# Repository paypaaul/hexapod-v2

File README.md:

# Hexapod v2

Robot esapode a 18 gradi di libertà (6 zampe × 3 servo MG996R), stampato in 3D e comandato da un ESP32-S3 con camera e una SSC-32. Progetto personale, in fase di progettazione CAD.

Altri render: [da dietro](docs/immagini/render-montato-post.png), [di fianco](docs/immagini/render-montato-fianco.png), [esploso della zampa](docs/immagini/render-esploso-zampa.png), [esploso del corpo](docs/immagini/render-esploso-corpo.png).

## Dove guardare

| Documento | Contenuto |
|---|---|
| [Progetto meccanico](docs/progetto-meccanico.md) | zampa, corpo, assieme, verifiche di movimento, cavi, massa |
| [Decisioni](docs/decisioni.md) | registro delle scelte con il perché |
| [BOM](docs/BOM.md) | distinta base, schema di alimentazione, viteria, domande aperte |
| [Studio dei componenti](docs/studio-componenti.md) | servo, alimentazione, batteria, giunti, stampa |
| [Dimensionamento](docs/dimensionamento.md) | massa, geometria, coppie e assetti |
| [Dimensioni dei componenti](docs/dimensioni-componenti.md) | quote dei componenti con la fonte |
| [Ricerca](docs/ricerca/) | proposte e revisioni indipendenti di zampa e corpo |

## Cartelle

- `cad/script/`: script Python che costruiscono il modello in Fusion (`corpo.py`, `zampa.py`, `assieme.py`).
- `cad/stl/`: STL delle parti già pronte per i provini.
- `cad/modelli/`: fonti dei modelli STEP di terzi.
- `cad/render/`: render schematici del modello.
- `calc/`: calcoli di statica, andature, escursioni e cavi.

Lo stato del lavoro e i prossimi passi sono in [CLAUDE.md](CLAUDE.md).

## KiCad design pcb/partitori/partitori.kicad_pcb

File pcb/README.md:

# Circuiti stampati (PCB)

Progetti KiCad delle schede del robot. Piano, scelte e fasi: `docs/piano-pcb.md` (D-078).

## Versione di KiCad

**KiCad 10.0.7**. Gli script e la CI usano questa; un'altra 10.0.x va provata prima (formato dei file, DRC).
Sul Mac: `/Applications/KiCad/KiCad.app`, con `kicad-cli` in `Contents/MacOS/` e il Python di KiCad (3.9, con `pcbnew`) in `Contents/Frameworks/Python.framework/Versions/Current/bin/python3`. I percorsi si cambiano con le variabili `KICAD_CLI`, `KICAD10_SYMBOL_DIR` e `KICAD10_FOOTPRINT_DIR`.

## Come sono fatti i progetti

Schema e PCB **si generano da script**, e i file di KiCad sono il risultato. Una modifica si fa nello script e si rigenera: una modifica fatta solo nell'editor si perde alla rigenerazione. L'editor serve per guardare (schema, PCB, 3D) e per provare; quello che si vuole tenere torna nello script.

| Passo | Script | Python |
|---|---|---|
| copie dei simboli e delle impronte standard in `librerie/` | `script/librerie.py` (`--controlla`; vuole le librerie di KiCad installate) | qualunque |
| simboli e impronte disegnati per il robot (ESP32 RE1.3, D24V22F5, PTC e 470 µF sdraiati) in `librerie/hex2.*` | `script/propri.py` (`--controlla`) | qualunque |
| schema: simboli, fili, etichette, segni di non collegato | `<scheda>/genera_schema.py`, con `script/schema_kicad.py` | qualunque, con `kicad-cli` |
| PCB: impronte con le reti della netlist, contorno, piste, vie, riempimenti | `<scheda>/genera_pcb.py`, con `script/scheda_kicad.py` | di KiCad (`pcbnew`) |
| ERC, DRC con la parità dello schema (se c'è già il PCB) e reti contro la guida | `script/controlla.py <cartella>` | qualunque, con `kicad-cli` |
| regole del DRC: fonte unica `regole/hex2.kicad_dru`, copiata in ogni progetto come `<nome>.kicad_dru` | `script/regole.py` (`--controlla`) | qualunque |
| contorno, fori Ø2,4 e zone senza rame dalle quote del CAD | `script/genera_contorni.py` (`--controlla <file>.kicad_pcb`); nel PCB `Scheda.contorni_dal_cad` | qualunque |
| reti di KiCad contro `guida/schemi/sorgenti/*_def.py`, con le differenze volute in `aggiunte.yaml` | `script/verifica_reti.py <scheda> <file>.net` | qualunque, con PyYAML |

Piazzamento sul lato B: KiCad ribalta l'impronta specchiando la Y; con 180 gradi in più la scheda si guarda dall'alto del robot (X specchiata). `pcb/stato.yaml` dice in che fase è ogni scheda: in "piazzamento" `controlla.py` conta a parte le connessioni da sbrogliare e gli avvisi di serigrafia.

Regole degli script:
- lo schema ha un tratto di filo e un'etichetta su ogni pin collegato, e il segno di non collegato sui pin liberi. Un pin senza né l'uno né l'altro, o una rete su un pin che non esiste, fermano il generatore prima di KiCad;
- gli identificativi sono ripetibili (uuid derivati dai nomi nello schema, generatore con il seme nel PCB): rigenerare senza modifiche dà gli stessi file;
- lo schema passa da `kicad-cli sch upgrade --force`, così è nel formato in cui lo salverebbe KiCad;
- il PCB copia nelle impronte quello che copierebbe "Aggiorna PCB dallo schema": percorso del simbolo, foglio, campi, esclusione dalla distinta, non montare;
- `controlla.py` fallisce su qualunque rilievo, anche sugli avvisi.

Terna: x = X del robot + 100, y = 100 − Y del robot (KiCad ha la Y verso il basso). Le schede si guardano dall'alto del robot; i componenti della scheda del carapace stanno sul retro (B.Cu). Lo STEP con `--user-origin 100x100mm` torna nella terna del robot (`cad/CLAUDE.md`, STEP delle PCB).

Numeri dei pin per `verifica_reti.py`: ESP32 (U1) da 1 a 20 la fila `ESP_L` dalla coda alla testa, da 21 a 40 la fila `ESP_R` nello stesso verso; D24V22F5 (U2) PG 1, EN 2, VIN 3, GND 4, VOUT 5; condensatori con il + sul pin 1; resistenze e diodi a due fori con il primo foro dei `*_def.py` sul pin 1 (per i diodi il catodo). Le impronte di U1 e U2 si fanno con questa numerazione.

Testata J2 del carapace: pad n = polo n del cavo piatto; poli dispari sulla fila lato chiave, a 4,38 dalla scatola (S-26). Da provare sulla dima con la spina (F5).

**Regole del DRC**: se una sola regola di `regole/hex2.kicad_dru` è scritta male, KiCad ignora tutto il file senza avvisi e il DRC esce a zero. Ogni modifica alle regole passa da `tests/test_pcb.py` (il caso della pista stretta usa la copia vera delle regole) e una regola nuova ha il suo caso di controllo.

Librerie: `librerie/hex2_kicad.kicad_sym` (simboli copiati da KiCad 10, appiattiti) e `librerie/hex2.pretty` (impronte copiate e, più avanti, quelle disegnate per il robot). Le tabelle `sym-lib-table` e `fp-lib-table` di ogni progetto puntano solo lì.

## Schede

| Cartella | Scheda | Stato |
|---|---|---|
| `prova/` | scheda di prova del metodo, caso di riferimento della CI | schema e PCB |
| `basetta/` | PCB-B, basetta dell'ESP32 (piano 4.1), **quattro strati** | schema (R1, D-079, ritocchi di F4 in D-083); piazzamento e sbroglio da script con DRC a zero (D-083); dima e stampe per R2; serigrafia da fare |
| `carapace/` | PCB-C, scheda del carapace (piano 4.2) | schema (R1, D-079), piazzamento e sbroglio da script con DRC a zero (D-082); dima, render e stampa 1:1 per R2 (F5) |
| `partitori/` | PCB-P, scheda dei partitori, **quattro strati** (sullo stesso pannello della basetta) | schema, piazzamento e sbroglio da script con DRC a zero (D-084), sagoma di prova fino alla 2.1.9 del CAD; dima e stampe |

## Prova del metodo (F1, 18 ottobre 2026)

Scheda di prova in `prova/`: buffer SN74AHCT125N a cinque unità (quattro porte e l'alimentazione) in DIP-14, ponticello a tre piazzole, resistenza a reoforo, condensatore 0805, strip 1 × 4, punto di prova, due PWR_FLAG.

| Passo del piano (5.2) | Esito |
|---|---|
| 1. schema da script, con simboli, etichette e fili, che passa l'ERC | **riuscito**: ERC a zero rilievi. La netlist di KiCad è uguale alle reti dello script. Caso di controllo: un pin scollegato e un'alimentazione senza PWR_FLAG danno 3 errori (`pin_not_connected`, `pin_not_driven`, `power_pin_not_driven`) |
| 2. PCB con le impronte e le reti assegnate alle piazzole da `pcbnew` | **riuscito**: impronte dalla libreria del progetto, percorso del simbolo, reti della netlist |
| 3. piste e riempimento di massa da script | **riuscito**: piste su F.Cu, due vie, riempimento su B.Cu riempito da `ZONE_FILLER` |
| 4. DRC con `--schematic-parity` a zero, e un caso di controllo che fallisce | **riuscito**: zero violazioni, zero connessioni mancanti, zero rilievi di parità. Controlli: una pista tolta dà 2 `unconnected_items`; una piazzola con la rete sbagliata dà corto, ponte di maschera, connessione mancante e `net_conflict` di parità |

**Esito: schema, piazzamento e sbroglio li fa l'agente da script**, e l'utente rivede nell'editor e nei render. La colonna "Chi" del piano resta com'è.

Cose imparate nella prova, che il codice già tiene in conto:
- `board.GetLayerID('F.SilkS')` dà UNDEFINED (vuole i nomi utente): si usano le costanti `pcbnew.F_SilkS`;
- `pcbnew.NewBoard(percorso)` apre il `.kicad_pro` accanto e lo completa con i valori predefiniti, senza togliere quelli scritti prima;
- le istanze dei simboli non devono portare `ki_keywords` e `ki_fp_filters`: KiCad le tiene solo nella libreria, e copiate nelle impronte danno avvisi di parità e scritte sulla serigrafia;
- ogni unità di un simbolo a più unità elenca tutti i pin del simbolo, altrimenti KiCad dà ai mancanti un uuid a caso;
- con `--exit-code-violations` il DRC esce con 5 solo per gli errori: i rilievi di parità sono avvisi. Per questo `controlla.py` legge il JSON.

## Sbroglio

Lo sbroglio della basetta si rifà con `$KP pcb/basetta/sbroglia.py` (circa 3 minuti) e scrive `basetta/piste.json`, che `genera_pcb.py` rimette nel PCB: la CI non ha bisogno di strumenti esterni. Passi:
1. `script/sbroglio.py`, instradatore a griglia del progetto (Python puro, A*, 0,1 mm, tratti a 45°), per le reti con le regole a coppie del `.kicad_dru`: potenza, VBAT a 1 mm, segnali a 5 V a 1 mm dai pin dell'ESP32;
2. `script/freerouting.py` con **Freerouting 2.5.0** (`~/tools/freerouting/freerouting-2.5.0.jar`, da github.com/freerouting/freerouting) e **OpenJDK di Homebrew** (`brew install openjdk`, Java 25 o successivo) per le altre reti. Telemetria spenta da riga di comando e in `~/Library/Application Support/freerouting/freerouting.json`; niente piste ristrette ai pin. La versione nativa `freerouting-cli` si blocca allo sbroglio (errore di serializzazione di GraalVM): non si usa;
3. di nuovo `sbroglio.py`, sui quattro strati, per le reti che Freerouting lascia aperte o con un errore.

Dopo `ImportSpecctraSES` gli oggetti di `pcbnew` di quel processo non si leggono più dal Python: la lettura e la rifinitura girano in un processo nuovo. Le classi di rete (larghezze, VBAT a 1 mm) stanno nel `.kicad_pro`, scritte da `genera_pcb.py`, perché Freerouting non legge il `.kicad_dru`.

## Dime (F5)

Prima di ordinare, ogni scheda si prova con una **dima stampata 1:1**: la sola scheda, senza rame, con la sagoma e i fori del PCB, nella terna del robot (`cad/stl/attrezzi/Dima_PCB_<Scheda>.stl`, da `script/dima.py`, Python di KiCad). I fori dei pin sono allargati di 0,4 mm (`gio_stampa` per lato), quelli Ø2,4 delle viti no: se la M2 passa e centra l'inserto nella dima, passa anche nella scheda. La dima è spessa 1,5 (la scheda 1,6). Con la dima ci sono i render e la stampa 1:1 (`script/stampe.py`, in `docs/immagini/pcb/`): la stampa va fatta al 100 % e controllata col righello sulla sagoma (PCB-C: 21,5 mm da coda a testa, 48 fra le punte delle ali).

**PCB-C** (`Dima_PCB_Carapace.stl`), cosa provare e cosa riportare:
1. **J2 Würth** infilata dal lato dei componenti (sotto, come nel robot): i 16 pin entrano senza forzare e la scatola arriva a filo del bordo di coda.
2. **Polo 1 di J2 (S-26)**: si innesta la spina IDC del cavo piatto (la chiave la fa entrare in un verso solo). Il polo 1 dell'impronta è il foro quadrato, sulla fila lontana dalla scatola, verso +Y. Col multimetro in continuità fra il filo rosso del cavo (polo 1) e i pin che escono dalla dima: il filo rosso deve dare continuità con il pin del foro quadrato. Se la dà con il pin accanto, sulla fila vicina alla scatola, l'impronta va rovesciata prima dell'ordine.
3. **CE1** (470 µF) in piedi sotto l'ala +Y, con il + sulla piazzola quadrata, e i due fili del pulsante nelle piazzole dell'ala −Y.
4. **Nel carapace** (quando è stampato, con gli inserti M2): quattro M2 × 4 sugli inserti; le viti centrano gli inserti, le ali non toccano, J2 sta nella sua sede, CE1 non tocca il dorso.

**PCB-B** (`Dima_PCB_Basetta.stl`):
1. **strip femmina** dell'ESP32 a 25,4 (P-005), con i contatti dei pin 27, 28, 30 e 40 sfilati (varchi, D-083); l'ESP32 RE1.3 innestato: si misurano i 8,5 mm e si guarda che U2, U3, il fusibile, D1 e le sei resistenze in piedi passino sotto il suo retro;
2. **D24V22F5** appoggiato sulla dima con i pin senza il distanziale: i componenti di sotto entrano nell'apertura e il modulo sta piano;
3. **U3** (DIP-14), PTC1 sdraiato, D1, le resistenze in piedi (alte non più di 7,5 dalla scheda) e R11, R12;
4. sul vassoio: quattro M2 × 5 nelle colonne, la dima appoggia piana e le code dei reofori non toccano.

Esito: una riga per prova (va / non va, con la misura se non va) in fondo a `docs/piano-pcb.md`.

## Comandi

```
KP=/Applications/KiCad/KiCad.app/Contents/Frameworks/Python.framework/Versions/Current/bin/python3
python3 pcb/script/librerie.py
python3 pcb/prova/genera_schema.py
$KP pcb/prova/genera_pcb.py
python3 pcb/script/controlla.py pcb/prova
$KP pcb/basetta/sbroglia.py
$KP pcb/partitori/sbroglia.py
python3 pcb/script/gerber.py basetta partitori carapace   # zip in build/gerber/ per jlcpcb.com
$KP pcb/script/dima.py carapace
python3 pcb/script/stampe.py carapace
python3 pcb/script/regole.py --controlla
.venv/bin/python -m pytest tests/test_pcb.py -q
```

Nella CI il job `pcb` installa KiCad dal PPA (`ppa:kicad/kicad-10.0-releases`, senza le librerie), controlla che la versione sia quella scritta qui sopra e fa regole, ERC e DRC di ogni progetto, contorni e `tests/test_pcb.py`. I rapporti JSON restano fra gli artefatti (`pcb-rapporti`).

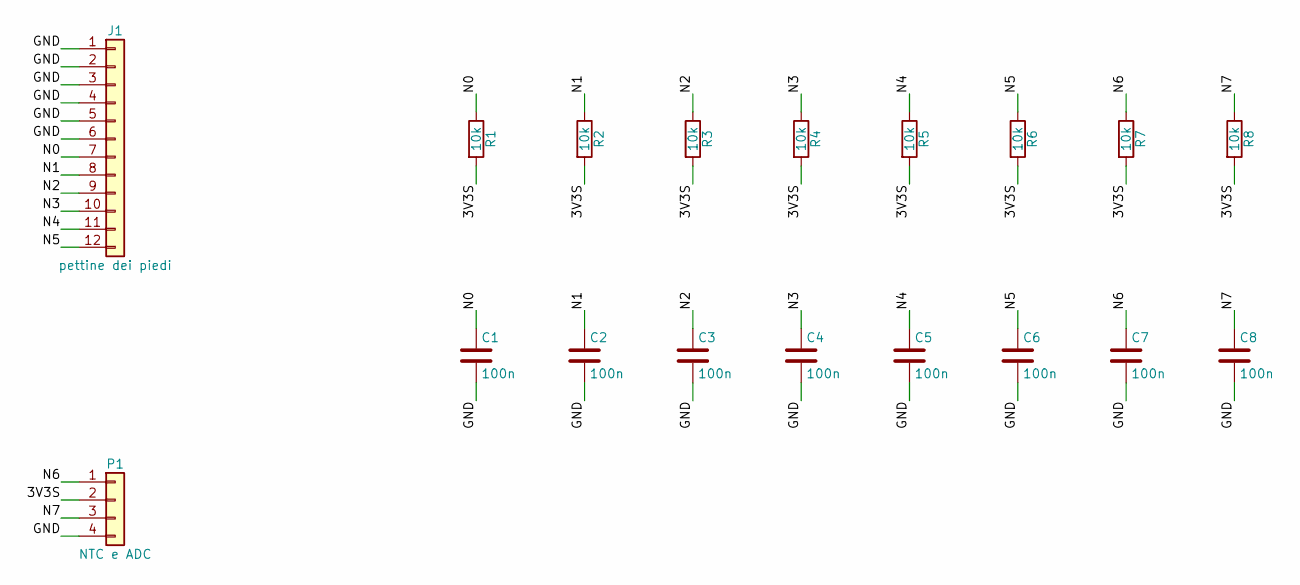
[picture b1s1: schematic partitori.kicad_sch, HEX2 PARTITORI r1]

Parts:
C1, C2, C3, C4, C5, C6, C7, C8: 100n; C_0805_2012Metric
J1: pettine dei piedi; Pettine_JR_2x06_P2.54_File5.08
P1: NTC e ADC; Fili_2x02_P2.54mm_D1.7
R1, R2, R3, R4, R5, R6, R7, R8: 10k; R_0805_2012Metric

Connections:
/3V3S: P1.2, R1.2, R2.2, R3.2, R4.2, R5.2, R6.2, R7.2, R8.2
/GND: C1.2, C2.2, C3.2, C4.2, C5.2, C6.2, C7.2, C8.2, J1.1, J1.2, J1.3, J1.4, J1.5, J1.6, P1.4
/N0: C1.1, J1.7, R1.1
/N1: C2.1, J1.8, R2.1
/N2: C3.1, J1.9, R3.1
/N3: C4.1, J1.10, R4.1
/N4: C5.1, J1.11, R5.1
/N5: C6.1, J1.12, R6.1
/N6: C7.1, P1.1, R7.1
/N7: C8.1, P1.3, R8.1

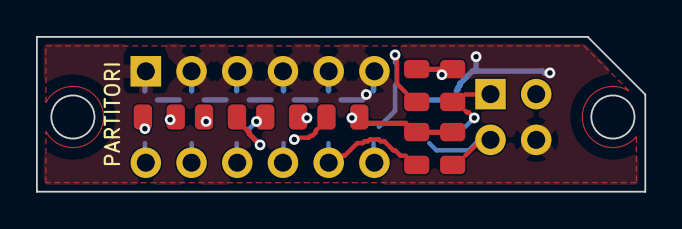
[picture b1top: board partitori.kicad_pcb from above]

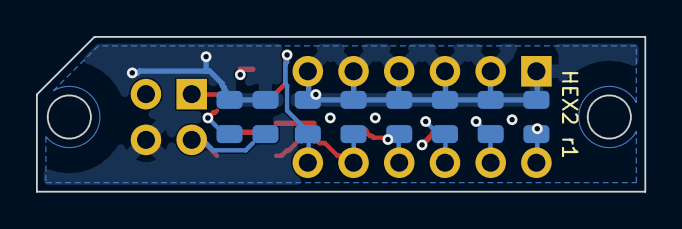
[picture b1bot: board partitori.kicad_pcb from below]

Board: 4 copper layers, 33.8 x 8.6 mm, 18 parts (8 on the bottom side), 10 nets.

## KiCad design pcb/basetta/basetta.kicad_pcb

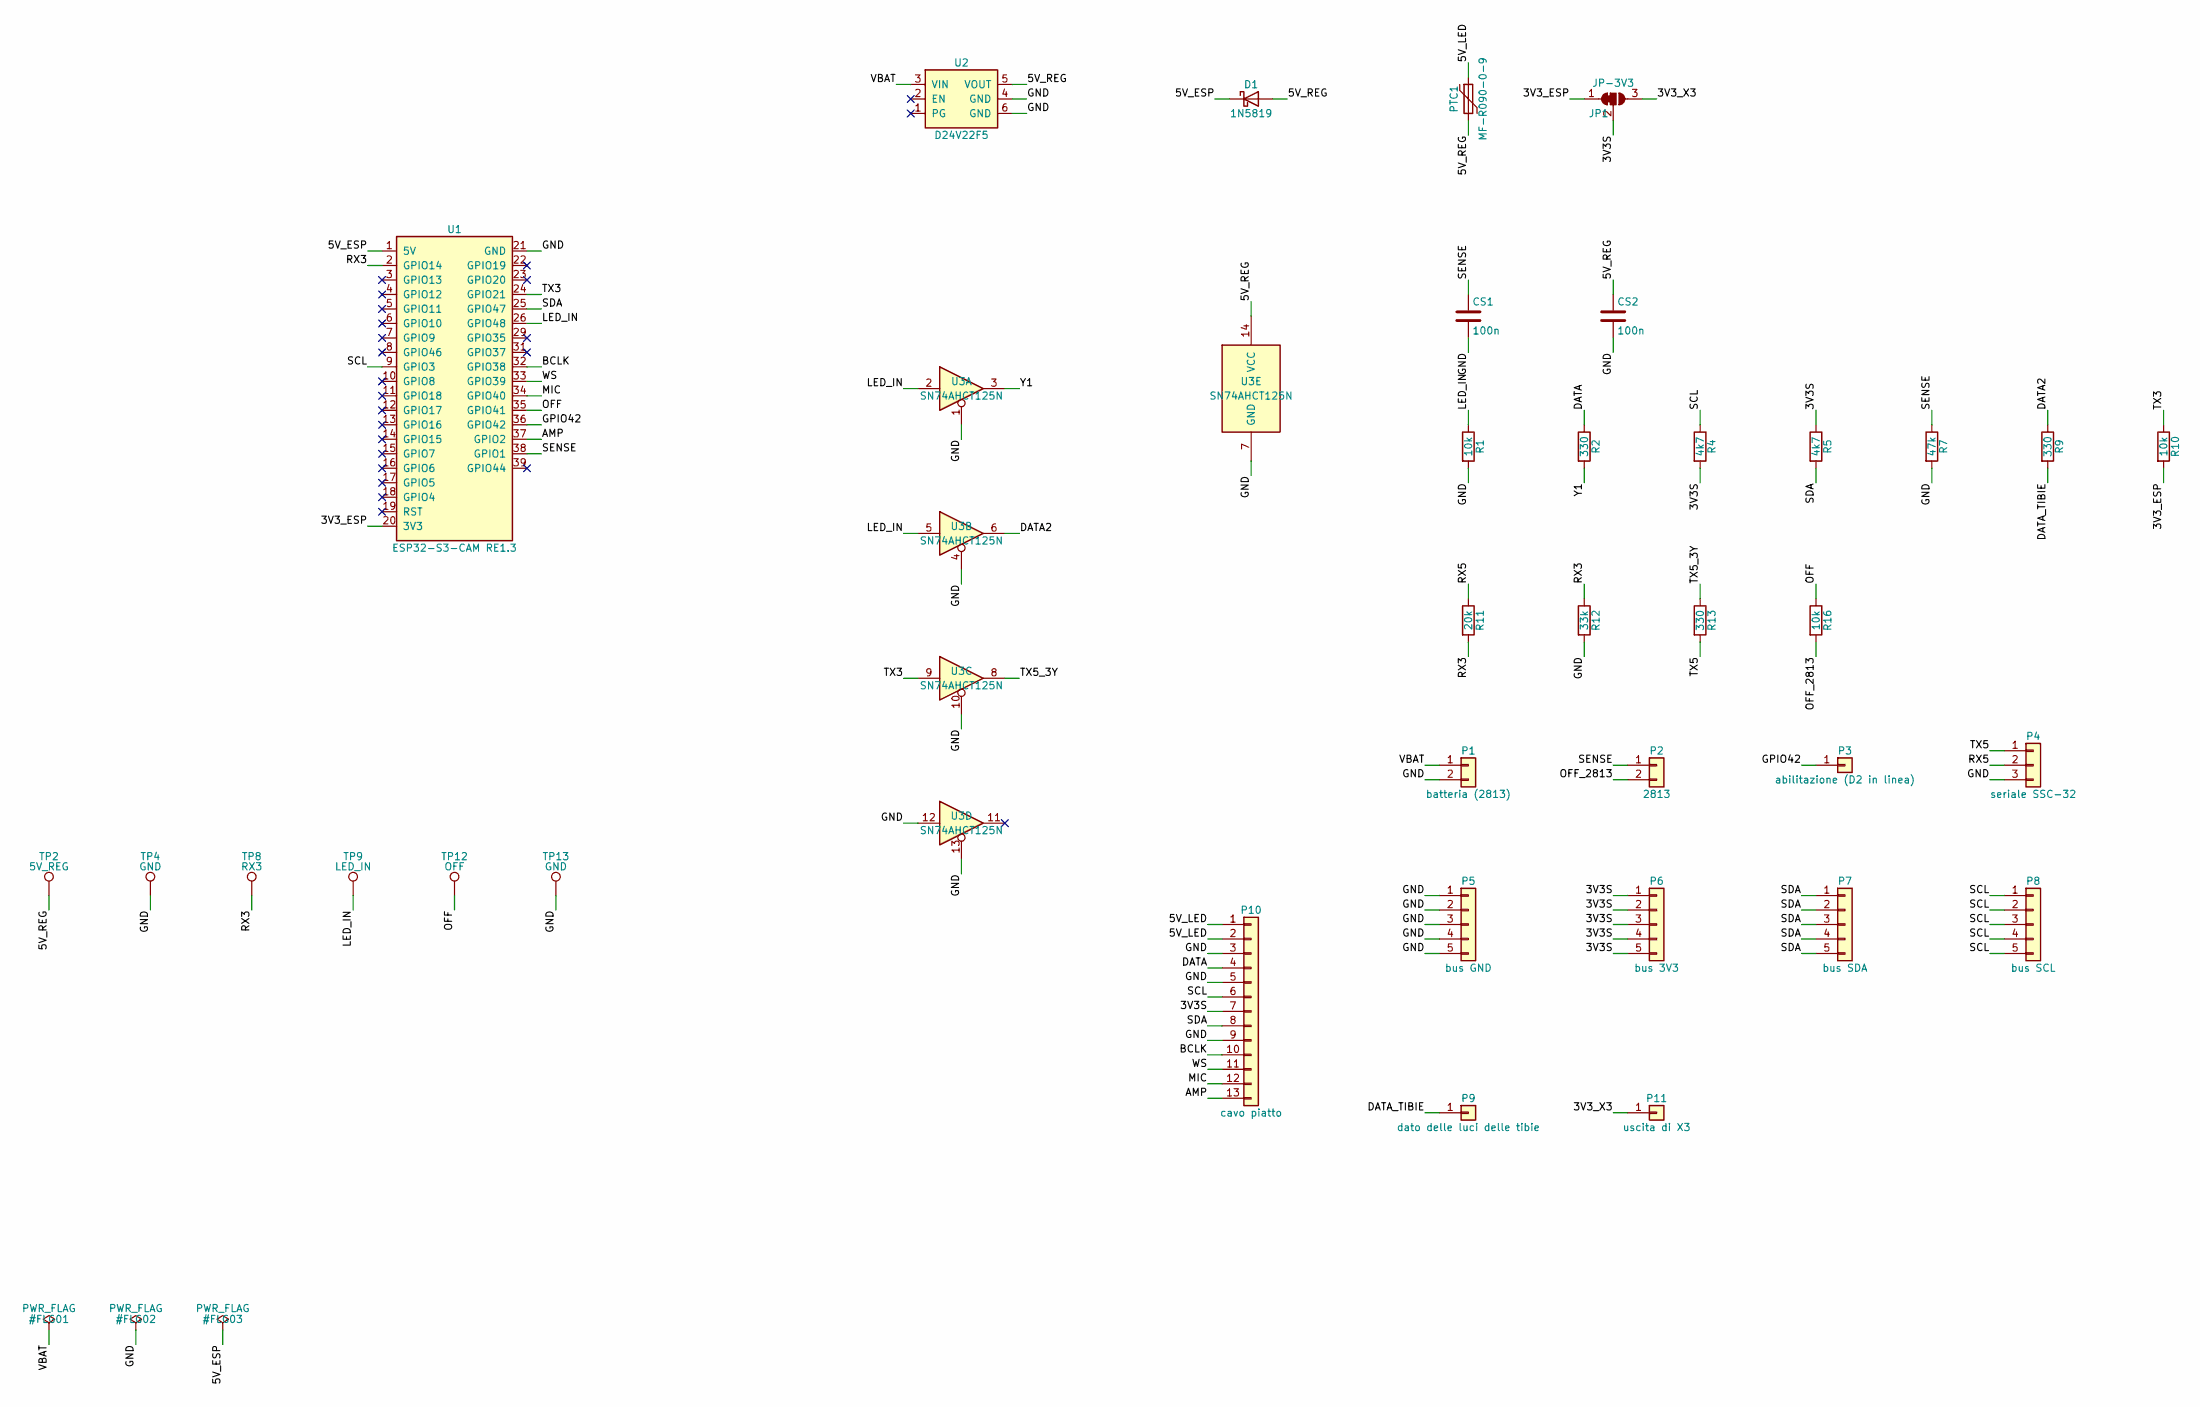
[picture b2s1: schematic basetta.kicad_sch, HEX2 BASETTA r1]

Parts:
CS1, CS2: 100n; C_0805_2012Metric
D1: 1N5819; D_DO-41_SOD81_P10.16mm_Horizontal
JP1: JP-3V3; SolderJumper-3_P1.3mm_Bridged12_RoundedPad1.0x1.5mm
P1: batteria (2813); Fili_1x02_P2.54mm_D1.7
P2: 2813; Fili_1x02_P2.54mm_D1.5
P3: abilitazione (D2 in linea); Fili_1x01_P2.54mm_D1.5
P4: seriale SSC-32; Fili_1x03_P2.54mm_D1.5
P5: bus GND; Fili_1x05_P2.54mm_D1.5
P6: bus 3V3; Fili_1x05_P2.54mm_D1.5
P7: bus SDA; Fili_1x05_P2.54mm_D1.5
P8: bus SCL; Fili_1x05_P2.54mm_D1.5
P9: dato delle luci delle tibie; Fili_1x01_P2.54mm_D1.5
P10: cavo piatto; Fili_1x13_P2.54mm_D1.7
P11: uscita di X3; Fili_1x01_P2.54mm_D1.5
PTC1: MF-R090-0-9; Fuse_Bourns_MF-R090-0-9_Sdraiato
R1, R10, R16: 10k; R_0805_2012Metric
R2, R9, R13: 330; R_Axial_DIN0207_L6.3mm_D2.5mm_P2.54mm_Vertical
R4, R5: 4k7; R_Axial_DIN0207_L6.3mm_D2.5mm_P2.54mm_Vertical
R7: 47k; R_Axial_DIN0207_L6.3mm_D2.5mm_P2.54mm_Vertical
R11: 20k; R_Axial_DIN0207_L6.3mm_D2.5mm_P7.62mm_Horizontal
R12: 33k; R_Axial_DIN0207_L6.3mm_D2.5mm_P7.62mm_Horizontal
TP2: 5V_REG; TestPoint_THTPad_1.5x1.5mm_Drill0.7mm
TP4, TP13: GND; TestPoint_THTPad_1.5x1.5mm_Drill0.7mm
TP8: RX3; TestPoint_THTPad_1.5x1.5mm_Drill0.7mm
TP9: LED_IN; TestPoint_THTPad_1.5x1.5mm_Drill0.7mm
TP12: OFF; TestPoint_THTPad_1.5x1.5mm_Drill0.7mm
U1: ESP32-S3-CAM RE1.3; ESP32_S3_CAM_RE13_Strip
U2: D24V22F5; Pololu_D24V22F5
U3: SN74AHCT125N; DIP-14_W7.62mm

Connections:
/3V3S: JP1.2 (C), P6.1, P6.2, P6.3, P6.4, P6.5, P10.7, R4.2, R5.1
/3V3_ESP: JP1.1 (A), R10.2, U1.20 (3V3)
/3V3_X3: JP1.3 (B), P11.1
/5V_ESP: D1.1 (K), U1.1 (5V)
/5V_LED: P10.1, P10.2, PTC1.1
/5V_REG: CS2.1, D1.2 (A), PTC1.2, TP2.1, U2.5 (VOUT), U3.14 (VCC)
/AMP: P10.13, U1.37 (GPIO2)
/BCLK: P10.10, U1.32 (GPIO38)
/DATA: P10.4, R2.1
/DATA2: R9.1, U3.6
/DATA_TIBIE: P9.1, R9.2
/GND: CS1.2, CS2.2, P1.2, P4.3, P5.1, P5.2, P5.3, P5.4, P5.5, P10.3, P10.5, P10.9, R1.2, R7.2, R12.2, TP4.1, TP13.1, U1.21 (GND), U2.4 (GND), U2.6 (GND), U3.1, U3.4, U3.7 (GND), U3.10, U3.12, U3.13
/GPIO42: P3.1, U1.36 (GPIO42)
/LED_IN: R1.1, TP9.1, U1.26 (GPIO48), U3.2, U3.5
/MIC: P10.12, U1.34 (GPIO40)
/OFF: R16.1, TP12.1, U1.35 (GPIO41)
/OFF_2813: P2.2, R16.2
/RX3: R11.2, R12.1, TP8.1, U1.2 (GPIO14)
/RX5: P4.2, R11.1
/SCL: P8.1, P8.2, P8.3, P8.4, P8.5, P10.6, R4.1, U1.9 (GPIO3)
/SDA: P7.1, P7.2, P7.3, P7.4, P7.5, P10.8, R5.2, U1.25 (GPIO47)
/SENSE: CS1.1, P2.1, R7.1, U1.38 (GPIO1)
/TX3: R10.1, U1.24 (GPIO21), U3.9
/TX5: P4.1, R13.2
/TX5_3Y: R13.1, U3.8
/VBAT: P1.1, U2.3 (VIN)
/WS: P10.11, U1.33 (GPIO39)
/Y1: R2.2, U3.3

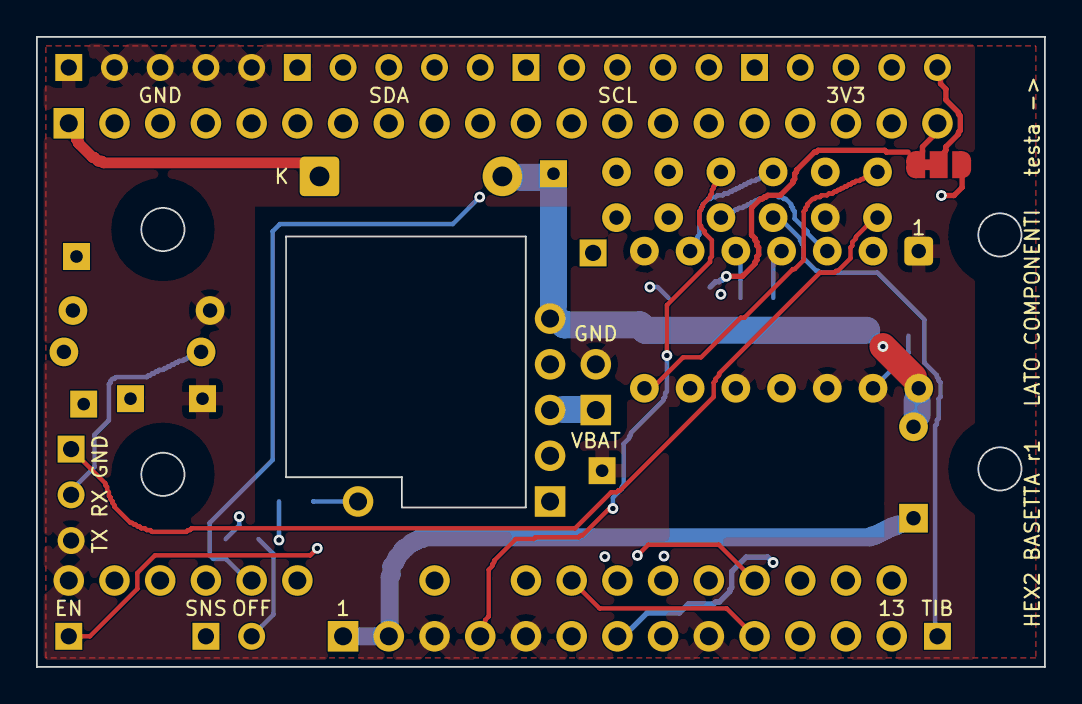
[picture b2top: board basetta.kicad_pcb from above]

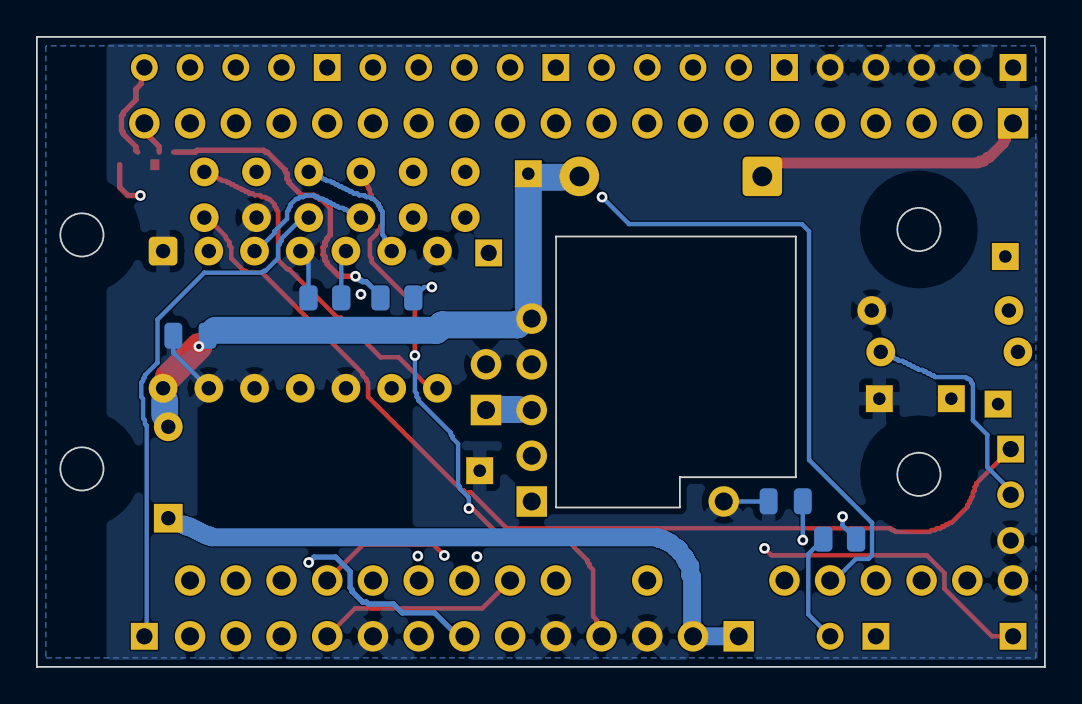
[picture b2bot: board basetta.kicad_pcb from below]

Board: 4 copper layers, 56.0 x 35.0 mm, 36 parts (6 on the bottom side), 28 nets.

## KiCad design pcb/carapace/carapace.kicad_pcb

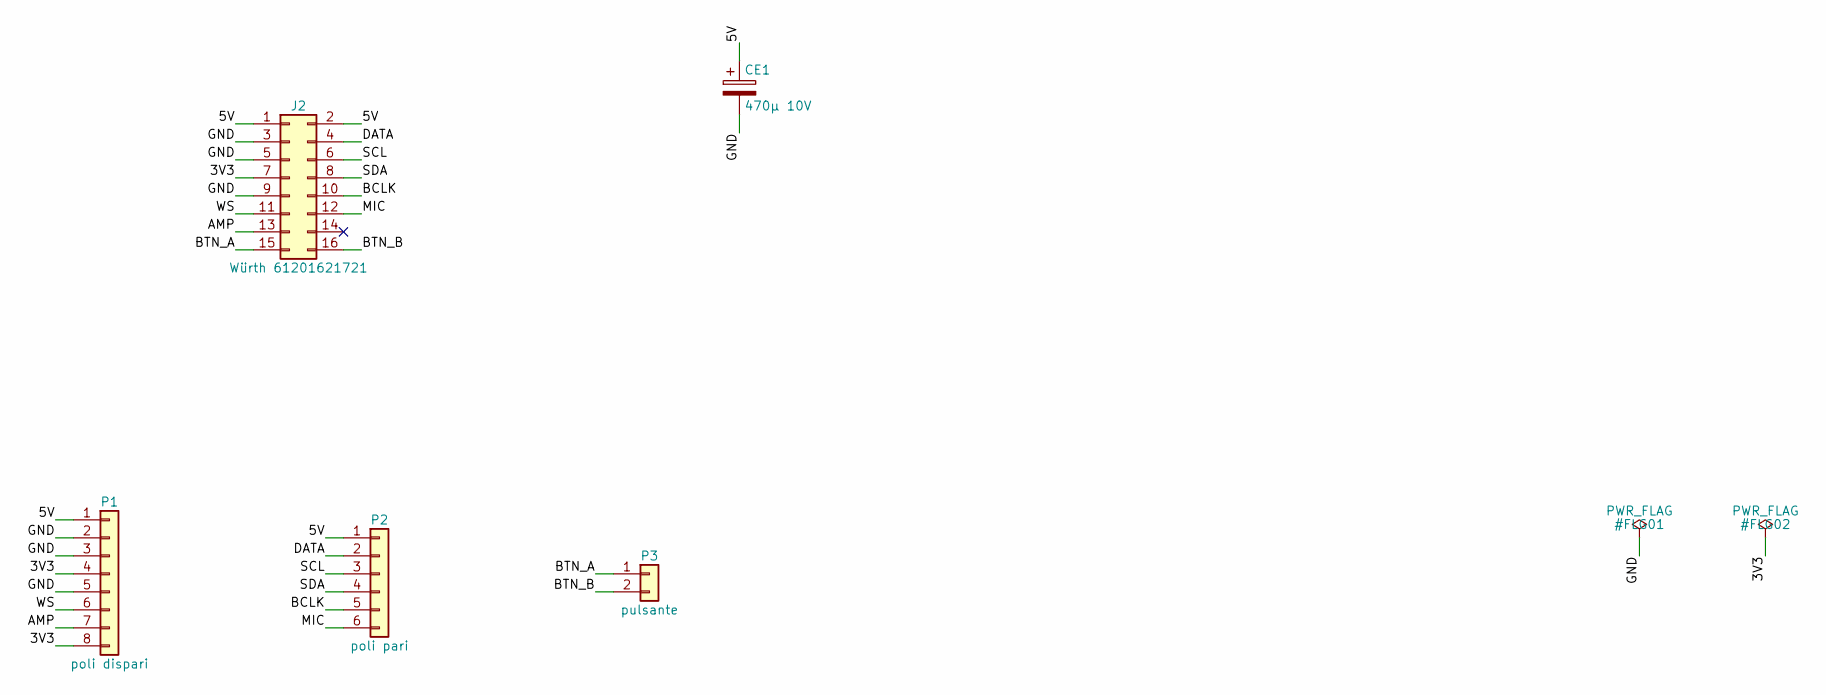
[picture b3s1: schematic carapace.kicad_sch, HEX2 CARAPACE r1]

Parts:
CE1: 470µ 10V; CP_Radial_D6.3mm_P2.50mm
J2: Würth 61201621721; IDC-Header_2x08_P2.54mm_Horizontal_Foro1.1
P1: poli dispari; Fili_1x08_P2.54mm_D1.7
P2: poli pari; Fili_1x06_P2.54mm_D1.7
P3: pulsante; Fili_1x02_P2.54mm_D1.7

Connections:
/3V3: J2.7, P1.4, P1.8
/5V: CE1.1, J2.1, J2.2, P1.1, P2.1
/AMP: J2.13, P1.7
/BCLK: J2.10, P2.5
/BTN_A: J2.15, P3.1
/BTN_B: J2.16, P3.2
/DATA: J2.4, P2.2
/GND: CE1.2, J2.3, J2.5, J2.9, P1.2, P1.3, P1.5
/MIC: J2.12, P2.6
/SCL: J2.6, P2.3
/SDA: J2.8, P2.4
/WS: J2.11, P1.6

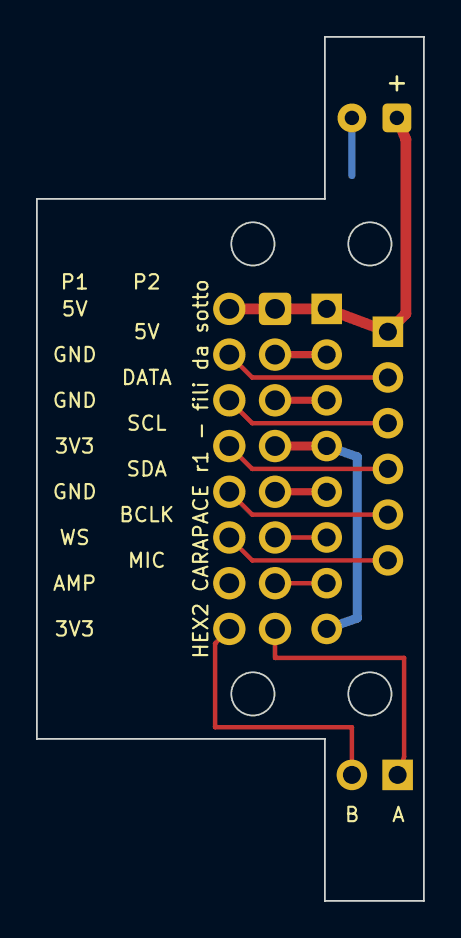
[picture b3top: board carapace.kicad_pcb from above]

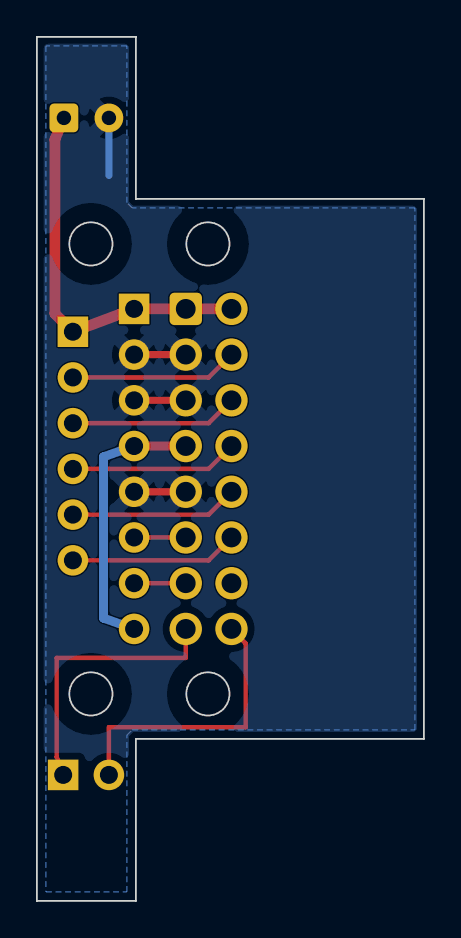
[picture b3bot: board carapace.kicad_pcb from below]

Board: 2 copper layers, 21.5 x 48.0 mm, 5 parts (5 on the bottom side), 12 nets.

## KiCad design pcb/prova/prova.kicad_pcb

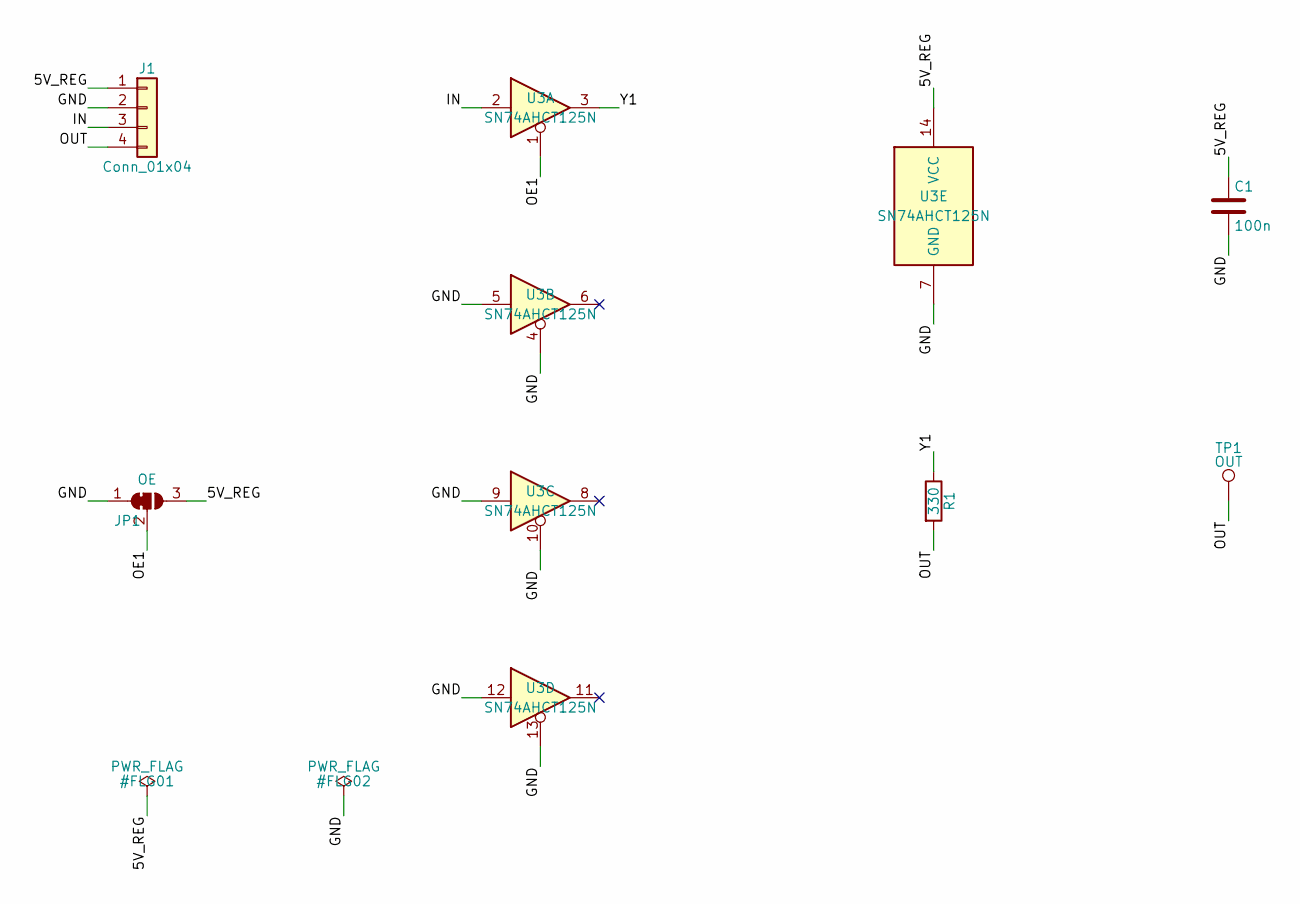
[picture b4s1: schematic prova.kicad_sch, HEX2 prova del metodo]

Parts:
C1: 100n; C_0805_2012Metric
J1: Conn_01x04; PinHeader_1x04_P2.54mm_Vertical
JP1: OE; SolderJumper-3_P1.3mm_Bridged12_RoundedPad1.0x1.5mm
R1: 330; R_Axial_DIN0207_L6.3mm_D2.5mm_P10.16mm_Horizontal
TP1: OUT; TestPoint_THTPad_1.5x1.5mm_Drill0.7mm
U3: SN74AHCT125N; DIP-14_W7.62mm

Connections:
/5V_REG: C1.1, J1.1, JP1.3 (B), U3.14 (VCC)
/GND: C1.2, J1.2, JP1.1 (A), U3.4, U3.5, U3.7 (GND), U3.9, U3.10, U3.12, U3.13
/IN: J1.3, U3.2
/OE1: JP1.2 (C), U3.1
/OUT: J1.4, R1.2, TP1.1
/Y1: R1.1, U3.3

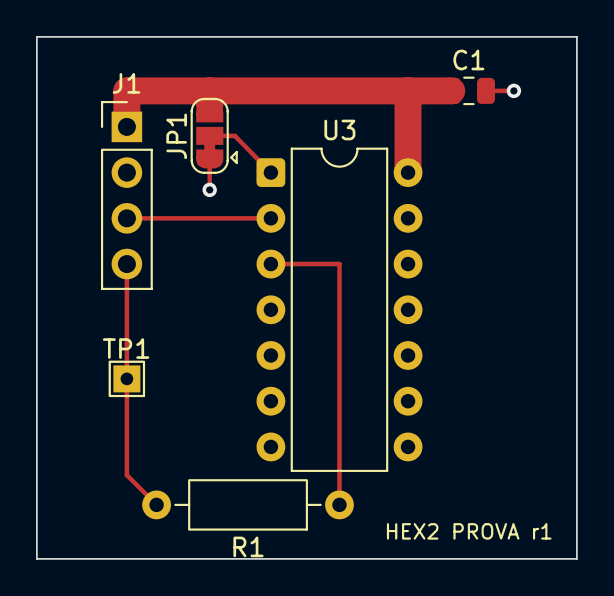
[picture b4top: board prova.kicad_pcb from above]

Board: 2 copper layers, 30.0 x 29.0 mm, 6 parts (0 on the bottom side), 6 nets.
